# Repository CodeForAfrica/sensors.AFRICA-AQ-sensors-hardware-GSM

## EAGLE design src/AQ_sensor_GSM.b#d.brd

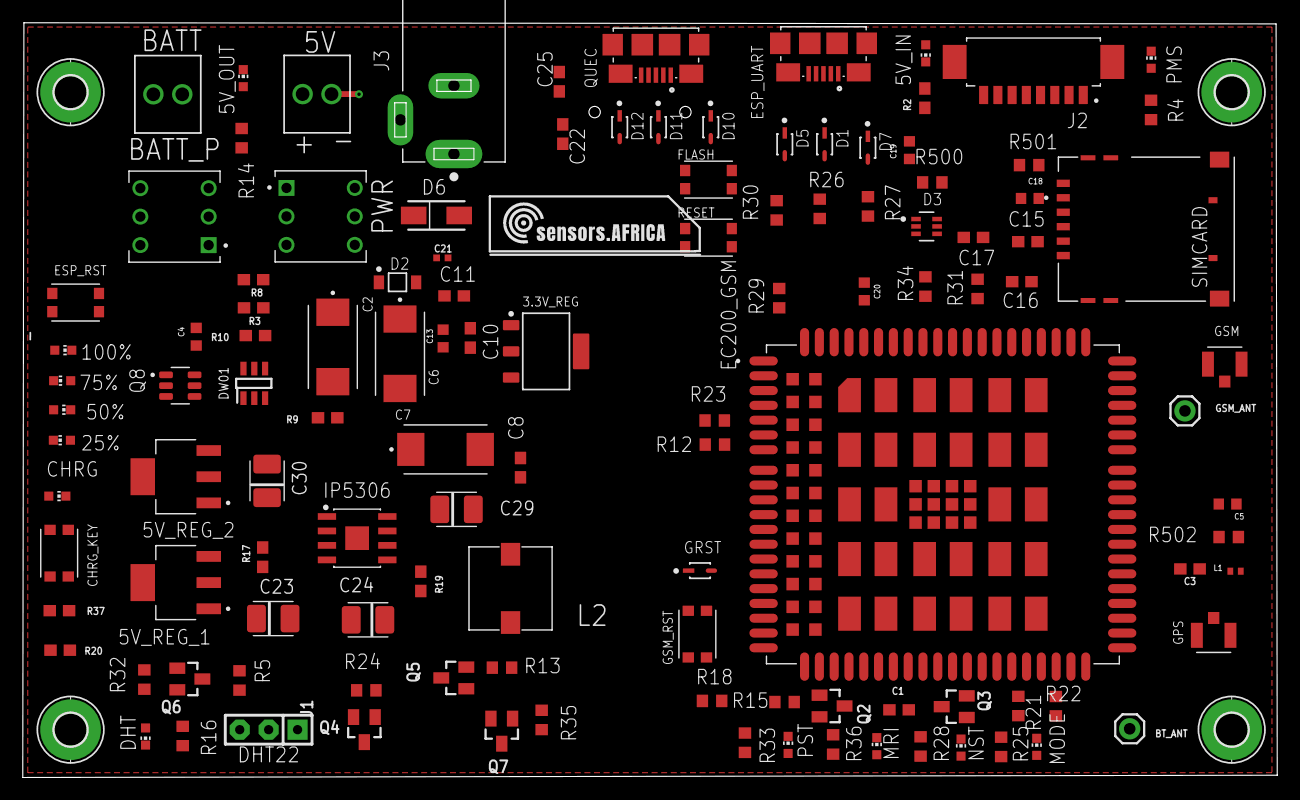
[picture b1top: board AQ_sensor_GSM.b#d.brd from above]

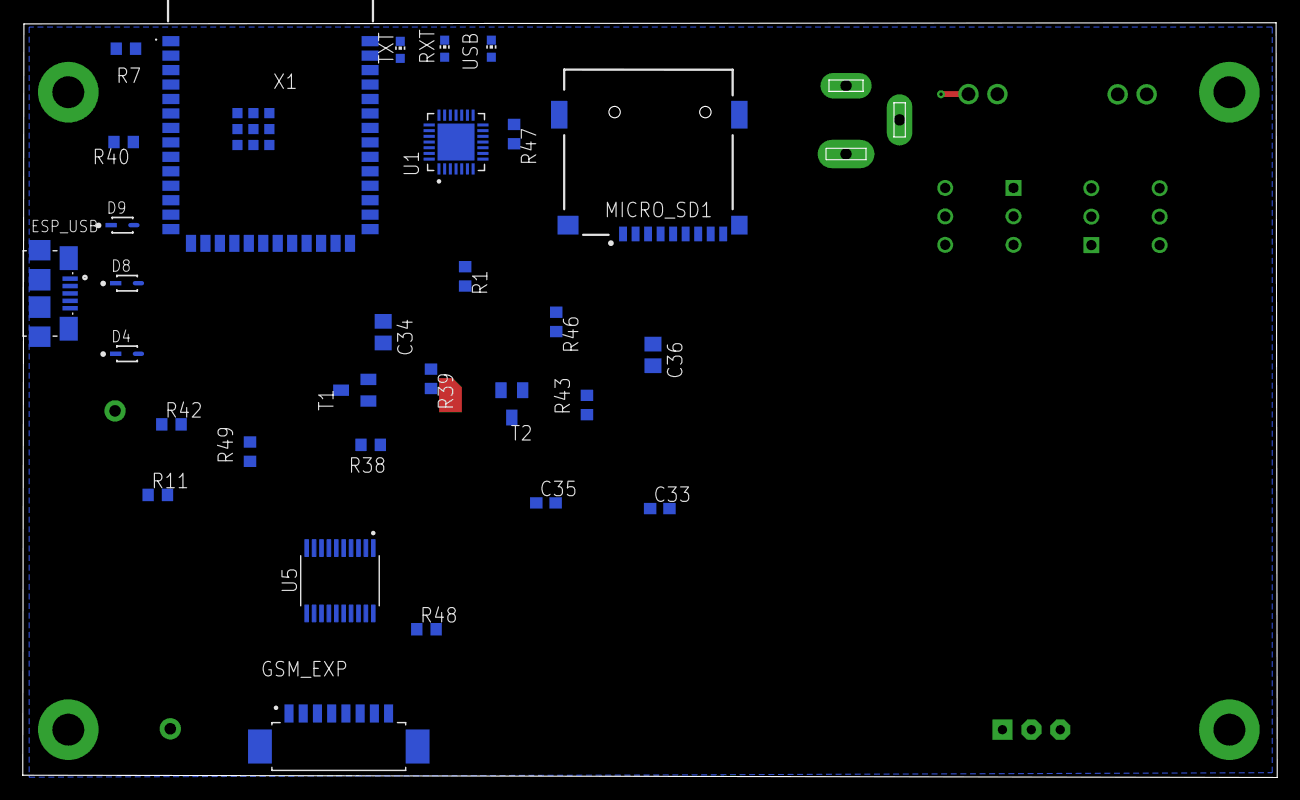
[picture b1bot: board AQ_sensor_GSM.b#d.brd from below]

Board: 4 copper layers, 110.2 x 66.3 mm, 151 parts (30 on the bottom side), 115 nets.

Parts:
3.3V_REG: TEXAS_INSTRUMENTS_LM1117IMP-3.3-NOPBTEXAS_INSTRUM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; TEXAS_INSTRUMENTS_LM1117IMP-3.3-NOPB_0
5V: 2828XX-2282834-2; TERMBLK_254-2N
5V_IN, 25%, 50%, 75%, 100%: ORANGE; CHIP-LED0603
5V_OUT: RED; CHIP-LED0603
5V_REG_1, 5V_REG_2: LM7805MPX/NOPB; VREG_LM7805MPX/NOPB
BATT: 2828XX-2282834-2; TERMBLK_254-2N
BATT_P: TL2285EE; SW_TL2285EE
BT_ANT: 1X01
C1: 10nF; 0603
C2, C6, C7: 20TQC100MYF; CAP_20TQC100MYF
C3: 100pF; 0603
C4, C5, C13, C18, C19, C20: 100nf; CAPC1608X90N
C8, C33, C35: 10uF; C0603
C10, C15, C16, C17: 33pF; C0603
C11: 10pF; C0603
C21: 22pF; 0402-TIGHT
C22: 0.1uF; C0603
C23, C24, C29, C30: TAJB106K016RNJ; CAP_TANT_B
C25: 1.0uF; C0603
C34, C36: 100nF; C0805
CHRG: ORANGE; CHIP-LED0603
CHRG_KEY: KMR621NGLFS; SW_KMR621NGLFS
D1, D4, D5, D7, D8, D9, D10, D11, D12: ON_SEMI_1N4148WSON_SEMI_1N4148WS_0_0; ON_SEMI_1N4148WS_0
D2: ON_SEMICONDUCTOR_MMSZ5231BT1GON_SEMICONDUCTOR_MMS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; ON_SEMICONDUCTOR_MMSZ5231BT1G_0
D3: SEMTECH_SMF05CSEMTECH_SMF05C_0_0; SEMTECH_SMF05C_0
D6: SS54-HF; DIOM5025X220N
DHT: GREEN; CHIP-LED0603
DW01: DW01-P; SOT23-6L
EC200_GSM: EC200UCNAB-N05-SNNSA; XCVR_EC200UCNAB-N05-SNNSA
ESP_RST: KMR621NGLFS; SW_KMR621NGLFS
ESP_UART: 10118192-0001LF; AMPHENOL_10118192-0001LF
ESP_USB: 10118192-0001LF; AMPHENOL_10118192-0001LF
FLASH: KMR621NGLFS; SW_KMR621NGLFS
GPS: 1909763-1; TE_1909763-1
GRST: ON_SEMI_1N4148WSON_SEMI_1N4148WS_0_0; ON_SEMI_1N4148WS_0
GSM: 1909763-1; TE_1909763-1
GSM_ANT: 1X01
GSM_EXP: 53261-0871; MOLEX_53261-0871
GSM_RST: KMR621NGLFS; SW_KMR621NGLFS
H1, H2, H3, H4: MOUNT-PAD-ROUND2.8; 2,8-PAD
IP5306: IP5306; SOIC127P600X165-9T209N
J1: F-1X03-SIP-100-32; SIP-100-03-32
J2: 53261-0871; MOLEX_53261-0871
J3: PJ-002BH; CUI_PJ-002BH
L1: LQW15AN47NG00D; INDC1005X60N
L2: 784778010
MICRO_SD1: TF-01A
MODE: ORANGE; CHIP-LED0603
MRI: ORANGE; CHIP-LED0603
NST: ORANGE; CHIP-LED0603
PMS: ORANGE; CHIP-LED0603
PST: ORANGE; CHIP-LED0603
PWR: TL2285EE; SW_TL2285EE
Q2, Q3, Q4, Q5, Q6, Q7: MMBT2222; SOT23-BEC
Q8: FS8205; SOT95P280X145-6N
QUEC: 10118192-0001LF; AMPHENOL_10118192-0001LF
R1: 0R; R0603
R2, R9: 1k; 0603
R3: 47k; 0603
R4, R16, R25, R28, R33, R36: 470R; R0603
R5, R12, R15, R21, R23, R31, R34, R500, R501: 4.7K; R0603
R7, R11, R49: 200; R0603
R8, R37: 10k; 0603
R10: 100R; 0603
R13, R18, R22, R24, R32, R35, R47: 47K; R0603
R14: 1K; R0603
R17, R19: 2R; 0603
R20: 220R; 0603
R26: 120K; R0603
R27, R38, R39, R40, R42, R43, R48: 10K; R0603
R29, R30: 51K; R0603
R46: 20K; R0603
R502: 10R; R0603
RESET: KMR621NGLFS; SW_KMR621NGLFS
RXT: CHIP-LED0603
SIMCARD: 78646-3001; MOLEX_78646-3001
T1, T2: S8050; SC59-BEC
TXT: CHIP-LED0603
U1: CP2102N-A02-GQFN28; QFN50P500X500X80-29N
U5: TXS0108EPWR; SOP65P640X120-20N
USB: CHIP-LED0603
X1: ESP32-S3-WROOM-1-N16R8; ESP32S3WROOM1N8R2

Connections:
5V0UT1: 5V_REG_1.3, 5V_REG_2.3, PWR.1, PWR.6
5V_IN: 5V.1, C21.1, C22.1, C25.1, C30.1, IP5306.1, PWR.3, PWR.4, R2.1, R17.2
5V_OUT: 3.3V_REG.3, C7.1, GSM_EXP.8, IP5306.8, J2.8, R14.2
+3V3: 3.3V_REG.2, 3.3V_REG.4, C8.1, C20.2, J1.3, MICRO_SD1.4, R1.2, R5.1, R7.2, R11.2, R42.2, R43.2, R48.2, R49.2, U5.19, X1.2
+5V: C33.2, C34.2, R46.1, U1.7
BATT-: BATT.2, C4.2, DW01.6, Q8.1
BMSV: R3.2, R8.1, X1.4
BT_ANT: BT_ANT.1, EC200_GSM.35
DHT_LED: R16.2, X1.30
DHT_OUT: J1.2, R5.2, X1.29
DTR: R38.1, T2.E, U1.28
ESP_RST: ESP_RST.2_1, ESP_RST.2_2, R42.1, RESET.1_1, RESET.1_2, T1.C, X1.3
ESP_RX: U1.26, X1.36
ESP_TX: U1.25, X1.37
EUART_D+: D5.1, ESP_UART.3, U1.4
EUART_D-: D1.1, ESP_UART.2, U1.5
EUSB_D+: ESP_USB.3, X1.14
EUSB_N: D8.1, ESP_USB.2
GND: 3.3V_REG.1, 5V.2, 5V_IN.C, 5V_OUT.C, 5V_REG_1.2, 5V_REG_1.4, 5V_REG_2.2, 5V_REG_2.4, C1.2, C2.2, C5.1, C6.2, C7.2, C8.2, C10.2, C11.2, C13.1, C15.2, C16.2, C17.2, C19.1, C20.1, C21.2, C22.2, C23.2, C24.2, C25.2, C29.2, C30.2, C33.1, C34.1, C35.1, C36.1, CHRG.C, CHRG_KEY.2_1, CHRG_KEY.2_2, D1.2, D2.2, D3.2, D4.2, D5.2, D7.2, D8.2, D9.2, D10.2, D11.2, D12.2, DHT.C, EC200_GSM.8, EC200_GSM.9, EC200_GSM.19, EC200_GSM.22, EC200_GSM.36, EC200_GSM.46, EC200_GSM.48, EC200_GSM.50, EC200_GSM.51, EC200_GSM.52, EC200_GSM.53, EC200_GSM.54, EC200_GSM.56, EC200_GSM.72, EC200_GSM.76, EC200_GSM.85, EC200_GSM.86, EC200_GSM.87, EC200_GSM.88, EC200_GSM.89, EC200_GSM.90, EC200_GSM.91, EC200_GSM.92, EC200_GSM.93, EC200_GSM.94, EC200_GSM.95, EC200_GSM.96, EC200_GSM.97, EC200_GSM.98, EC200_GSM.99, EC200_GSM.100, EC200_GSM.101, EC200_GSM.102, EC200_GSM.103, EC200_GSM.104, EC200_GSM.105, EC200_GSM.106, EC200_GSM.107, EC200_GSM.108, EC200_GSM.109, EC200_GSM.110, EC200_GSM.111, EC200_GSM.112, ESP_RST.1_1, ESP_RST.1_2, ESP_UART.4, ESP_UART.5, ESP_UART.SH1, ESP_UART.SH2, ESP_UART.SH3, ESP_UART.SH4, ESP_UART.SH5, ESP_UART.SH6, ESP_USB.4, ESP_USB.5, ESP_USB.SH1, ESP_USB.SH2, ESP_USB.SH3, ESP_USB.SH4, ESP_USB.SH5, ESP_USB.SH6, FLASH.2_1, FLASH.2_2, GPS.2, GPS.3, GRST.2, GSM.2, GSM.3, GSM_EXP.7, GSM_RST.1_1, GSM_RST.1_2, H1.B2,8, H2.B2,8, H3.B2,8, H4.B2,8, IP5306.9, J1.1, J2.7, J3.2, J3.3, MICRO_SD1.6, PMS.C, Q2.E, Q3.E, Q4.E, Q5.E, Q6.E, Q7.E, Q8.3, QUEC.4, QUEC.5, QUEC.SH1, QUEC.SH2, QUEC.SH3, QUEC.SH4, QUEC.SH5, QUEC.SH6, R8.2, R9.2, R13.1, R18.1, R22.1, R24.1, R26.2, R29.2, R30.2, R32.1, R35.1, R40.2, R47.2, RESET.2_1, RESET.2_2, SIMCARD.C5, SIMCARD.G1, SIMCARD.G2, SIMCARD.G3, SIMCARD.G4, SIMCARD.G5, SIMCARD.G6, U1.3, U1.29, U5.11, USB.C, X1.1, X1.40, X1.41, X1.42, X1.43, X1.44, X1.45, X1.46, X1.47, X1.48, X1.49
GNSS_ANT: C3.2, EC200_GSM.47
GSM_ANT: EC200_GSM.49, GSM.1, GSM_ANT.1
GSM_RST: EC200_GSM.20, GRST.1, GSM_RST.2_1, GSM_RST.2_2, Q2.C
GSM_RST_O: R15.1, X1.35
G_ADC0: EC200_GSM.45, GSM_EXP.3
G_ADC1: EC200_GSM.44, GSM_EXP.4
G_I2C_SCL: EC200_GSM.41, GSM_EXP.6
G_I2C_SDA: EC200_GSM.42, GSM_EXP.5
G_USB_BOOT: EC200_GSM.115, GSM_EXP.2
G_USB_D+: D10.1, EC200_GSM.69, QUEC.3
G_USB_D-: D11.1, EC200_GSM.70, QUEC.2
G_USB_VBUS: EC200_GSM.71, GSM_EXP.1
IO0: FLASH.1_1, FLASH.1_2, R43.1, T2.C, X1.27
IO15: R40.1, X1.8
LBV: BATT.1, BATT_P.3, BATT_P.4, R3.1, R10.2
MAIN_CTS: EC200_GSM.64, U5.4
MAIN_DCD: EC200_GSM.63, U5.3
MAIN_DTR: EC200_GSM.66, U5.6
MAIN_RI: EC200_GSM.62, R34.1, U5.1
MAIN_RTS: EC200_GSM.65, U5.5
MAIN_RXD: EC200_GSM.68, U5.8
MAIN_TXD: EC200_GSM.67, U5.7
MCU-RXD_N: U5.14, X1.10
MCU-TXD_P: U5.13, X1.11
MCU_DTR: U5.15, X1.22
unnamed: Q2.B, R15.2, R18.2
unnamed: Q3.B, R21.2, R22.2
unnamed: L1.2, R502.1
unnamed: PMS.A, R4.1
unnamed: DW01.1, Q8.6
unnamed: C3.1, GPS.1, L1.1
unnamed: 5V_IN.A, R2.2
unnamed: C23.1, R17.1
unnamed: 25%.C, 50%.A, 75%.C, 100%.A, IP5306.4
unnamed: 25%.A, 50%.C, IP5306.2
unnamed: 75%.A, 100%.C, IP5306.3
unnamed: DW01.3, Q8.4
unnamed: CHRG_KEY.1_1, CHRG_KEY.1_2, R37.1
unnamed: IP5306.7, L2.1
unnamed: Q5.B, R12.2, R13.2
unnamed: C24.1, R19.1
unnamed: 5V_OUT.A, R14.1
unnamed: Q4.B, R23.2, R24.2
unnamed: DHT.A, R16.1
unnamed: Q6.B, R31.2, R32.2
unnamed: Q4.C, R25.1
unnamed: MODE.C, R25.2
unnamed: R26.1, R27.2, U5.10
unnamed: Q6.C, R33.1
unnamed: Q5.C, R28.1
unnamed: NST.C, R28.2
unnamed: 5V_REG_1.1, 5V_REG_2.1, D6.1
unnamed: C4.1, DW01.5, R10.1
unnamed: R7.1, USB.A
unnamed: PST.C, R33.2
unnamed: R30.1, U5.9
unnamed: R29.1, U5.12
unnamed: Q7.B, R34.2, R35.2
unnamed: Q7.C, R36.1
unnamed: MRI.C, R36.2
unnamed: IP5306.5, R20.2, R37.2
unnamed: CHRG.A, R20.1
unnamed: DW01.2, R9.1
unnamed: R38.2, T1.B
unnamed: R39.2, T2.B
unnamed: R48.1, U1.9
unnamed: R46.2, R47.1, U1.8
unnamed: R11.1, TXT.C
unnamed: R49.1, RXT.C
unnamed: TXT.A, U1.19
unnamed: RXT.A, U1.18
unnamed: D6.2, J3.1
unnamed: C35.2, C36.2, R1.1, U1.6
NETSTAT: EC200_GSM.6, R12.1
NET_MODE: EC200_GSM.5, R23.1
PMS_LED: R4.2, X1.28
PMS_RX: J2.5, X1.26
PMS_TX: J2.4, X1.23
PWRKEY: C1.1, EC200_GSM.21, Q3.C
PWRKEY_0: R21.1, X1.9
PWRSTAT: EC200_GSM.61, R31.1
RTS: R39.1, T1.E, U1.24
SD_CLK: MICRO_SD1.5, X1.31
SD_CS: MICRO_SD1.2, X1.32
SD_MISO: MICRO_SD1.3, X1.33
SD_MOSI: MICRO_SD1.7, X1.34
SHIELD: MICRO_SD1.MP1, MICRO_SD1.MP2, MICRO_SD1.MP3, MICRO_SD1.MP4
SIMCLK: C16.1, D3.3, EC200_GSM.16, SIMCARD.C3
SIMDATA: C15.1, D3.4, EC200_GSM.15, R501.1, SIMCARD.C7
SIMRST: C17.1, D3.5, EC200_GSM.17, SIMCARD.C2
USIM_DET: D3.6, EC200_GSM.13, R500.1
USIM_GND: C18.1, EC200_GSM.10
USIM_VDD: C18.2, D3.1, EC200_GSM.14, R501.2, SIMCARD.C1
VDD_EXT: C19.2, EC200_GSM.7, R27.1, R500.2, U5.2
VUSB: D7.1, D9.1, D12.1, ESP_UART.1, ESP_USB.1, PWR.2, PWR.5, QUEC.1
V_LIPO: BATT_P.2, BATT_P.5, C2.1, C5.2, C6.1, C10.1, C11.1, C13.2, C29.1, D2.1, EC200_GSM.57, EC200_GSM.58, EC200_GSM.59, EC200_GSM.60, IP5306.6, L2.2, MODE.A, MRI.A, NST.A, PST.A, R19.2, R502.2

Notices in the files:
parts and their libraries:
SparkFun-Connectors: Licensing: Creative Commons ShareAlike 4.0 International - https://creativecommons.org/licenses/by-sa/4.0
